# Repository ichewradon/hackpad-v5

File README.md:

# 

My macropad for 3D Modelling with 12 keys in a 4x4 cross, 1 rotary encoder and a LED backlight.

## Features:
- 8 SK6812 MINI-E LEDs for dynamic LED effects
  - Rainbow / Custom Gradient
  - Static Colour
- 1 EC11 Rotary Encoder to control volume with a custom printed dial
- 12 Individually Addressable Keys in a 4x4 cross
- [QMK Firmware](https://github.com/qmk/qmk_firmware) to allow for web-app control and memory after restart

## Overview

This is my hackpad in Fusion360 showing how it's assembled. 

## Case Model

This is my Case Model I made in Fusion360:

## PCB (Printed Circuit Board)

Here's my PCB. It was made in KiCad. The silkscreen was imported from separate vectors.

Schematic:

PCB:

## BoM (Bill of Materials)
- 12x MX-Style Switches
- 12x DSA Keycaps
- 1x EC11 Rotary Encoder
- 13x 1N4148 Diodes
- 8x SK6812 MINI-E LEDs
- 1x Seeed XIAO RP2040

<div align="center">
  
</div>

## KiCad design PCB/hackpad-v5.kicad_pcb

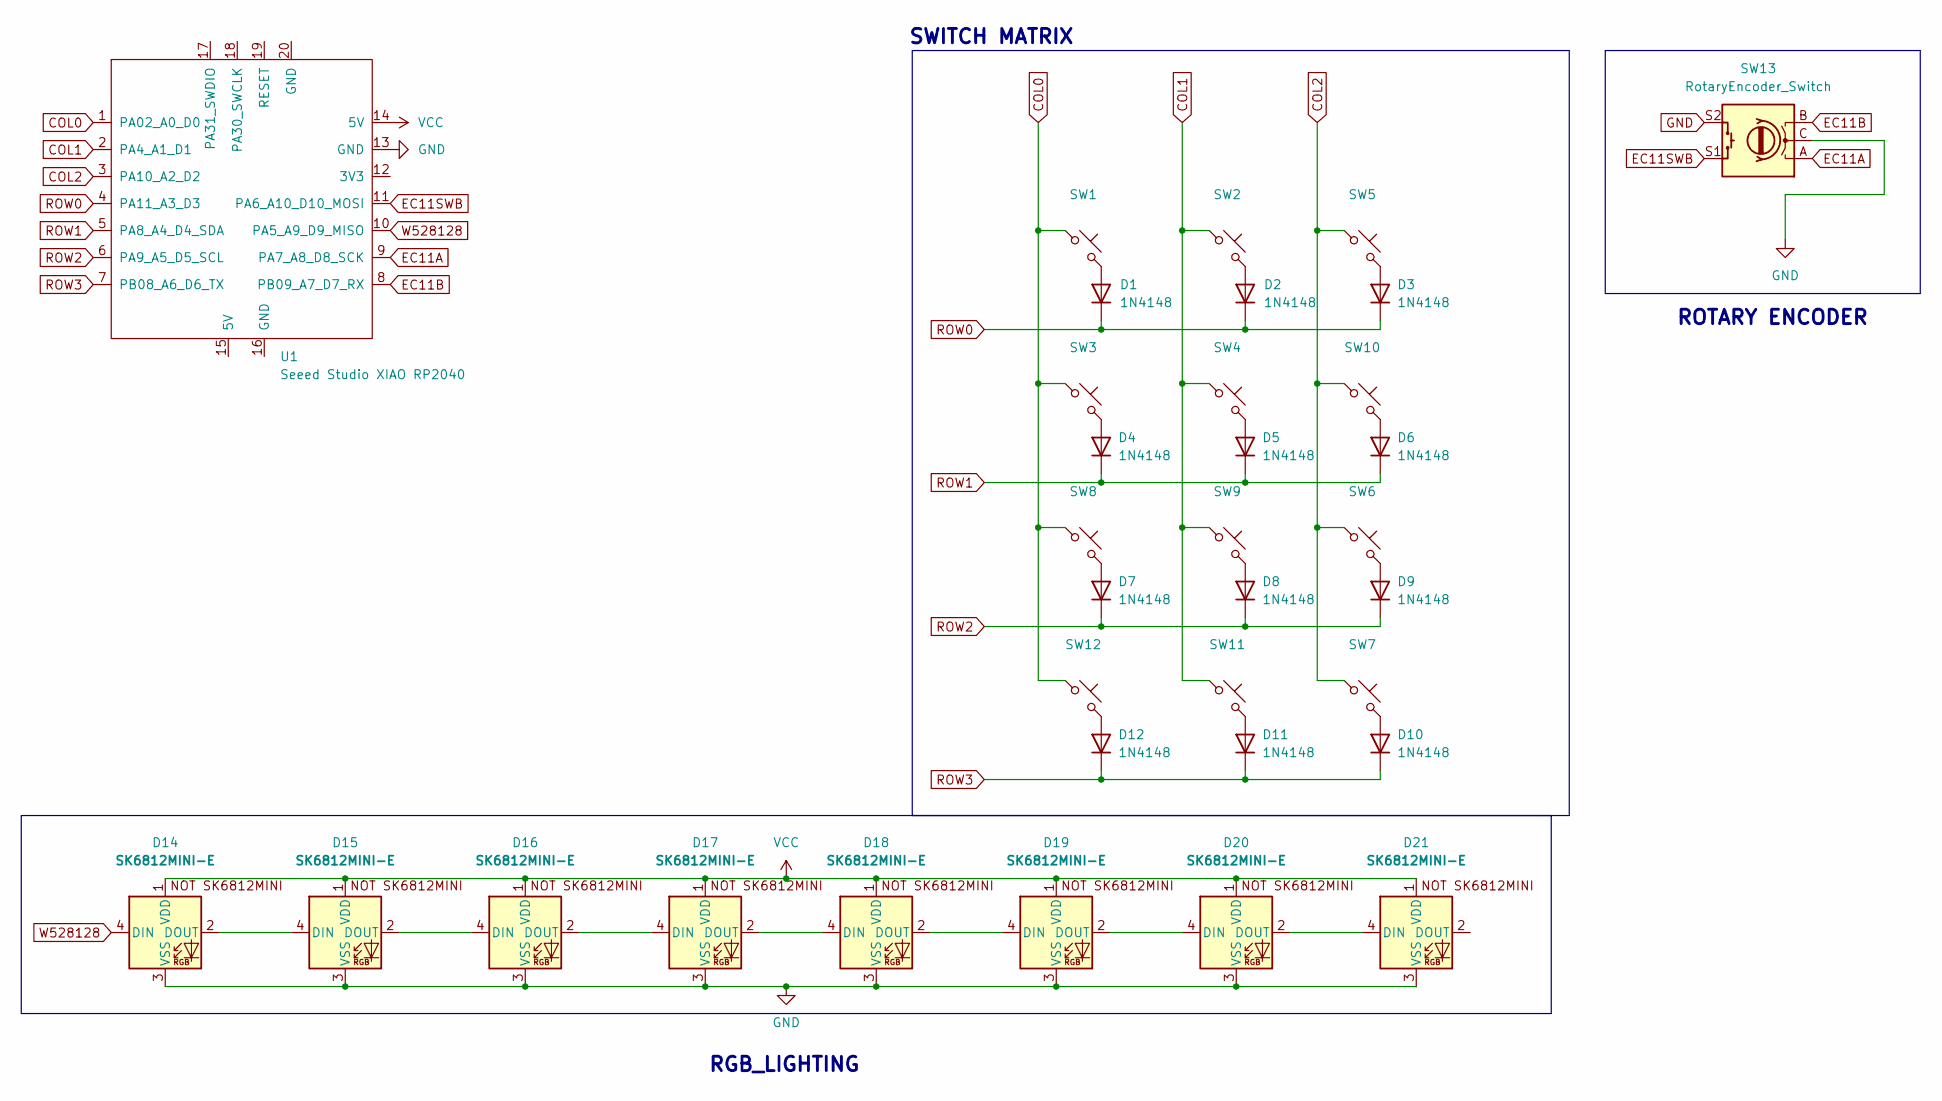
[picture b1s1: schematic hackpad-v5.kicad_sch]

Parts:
D1, D2, D3, D4, D5, D6, D7, D8, D9, D10, D11, D12: 1N4148; D_DO-35_SOD27_P7.62mm_Horizontal
D14, D15, D16, D17, D18, D19, D20, D21: SK6812MINI-E; SK6812MINI-E_fixed
SW1, SW2, SW3, SW4, SW5, SW6, SW7, SW8, SW9, SW10, SW11, SW12: SW_Push_45deg; SW_Cherry_MX_1.00u_PCB
SW13: RotaryEncoder_Switch; RotaryEncoder_Alps_EC11E-Switch_Vertical_H20mm
U1: Seeed Studio XIAO RP2040; XIAO-Generic-Hybrid-14P-2.54-21X17.8MM

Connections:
COL0: SW1.1, SW3.1, SW8.1, SW12.1, U1.1 (PA02_A0_D0)
COL1: SW2.1, SW4.1, SW9.1, SW11.1, U1.2 (PA4_A1_D1)
COL2: SW5.1, SW6.1, SW7.1, SW10.1, U1.3 (PA10_A2_D2)
EC11A: SW13.A, U1.9 (PA7_A8_D8_SCK)
EC11B: SW13.B, U1.8 (PB09_A7_D7_RX)
EC11SWA: U1.12 (3V3)
EC11SWB: SW13.S1, U1.11 (PA6_A10_D10_MOSI)
GND: D14.3 (VSS), D15.3 (VSS), D16.3 (VSS), D17.3 (VSS), D18.3 (VSS), D19.3 (VSS), D20.3 (VSS), D21.3 (VSS), SW13.C, SW13.S2, U1.13 (GND)
unnamed: D1.2 (A), SW1.2
unnamed: D2.2 (A), SW2.2
unnamed: D3.2 (A), SW5.2
unnamed: D4.2 (A), SW3.2
unnamed: D5.2 (A), SW4.2
unnamed: D6.2 (A), SW10.2
unnamed: D7.2 (A), SW8.2
unnamed: D8.2 (A), SW9.2
unnamed: D9.2 (A), SW6.2
unnamed: D10.2 (A), SW7.2
unnamed: D11.2 (A), SW11.2
unnamed: D12.2 (A), SW12.2
unnamed: D14.2 (DOUT), D15.4 (DIN)
unnamed: D15.2 (DOUT), D16.4 (DIN)
unnamed: D16.2 (DOUT), D17.4 (DIN)
unnamed: D17.2 (DOUT), D18.4 (DIN)
unnamed: D18.2 (DOUT), D19.4 (DIN)
unnamed: D19.2 (DOUT), D20.4 (DIN)
unnamed: D20.2 (DOUT), D21.4 (DIN)
ROW0: D1.1 (K), D2.1 (K), D3.1 (K), U1.4 (PA11_A3_D3)
ROW1: D4.1 (K), D5.1 (K), D6.1 (K), U1.5 (PA8_A4_D4_SDA)
ROW2: D7.1 (K), D8.1 (K), D9.1 (K), U1.6 (PA9_A5_D5_SCL)
ROW3: D10.1 (K), D11.1 (K), D12.1 (K), U1.7 (PB08_A6_D6_TX)
VCC: D14.1 (VDD), D15.1 (VDD), D16.1 (VDD), D17.1 (VDD), D18.1 (VDD), D19.1 (VDD), D20.1 (VDD), D21.1 (VDD), U1.14 (5V)
W528128: D14.4 (DIN), U1.10 (PA5_A9_D9_MISO)

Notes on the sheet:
ROTARY ENCODER
SWITCH MATRIX
RGB_LIGHTING

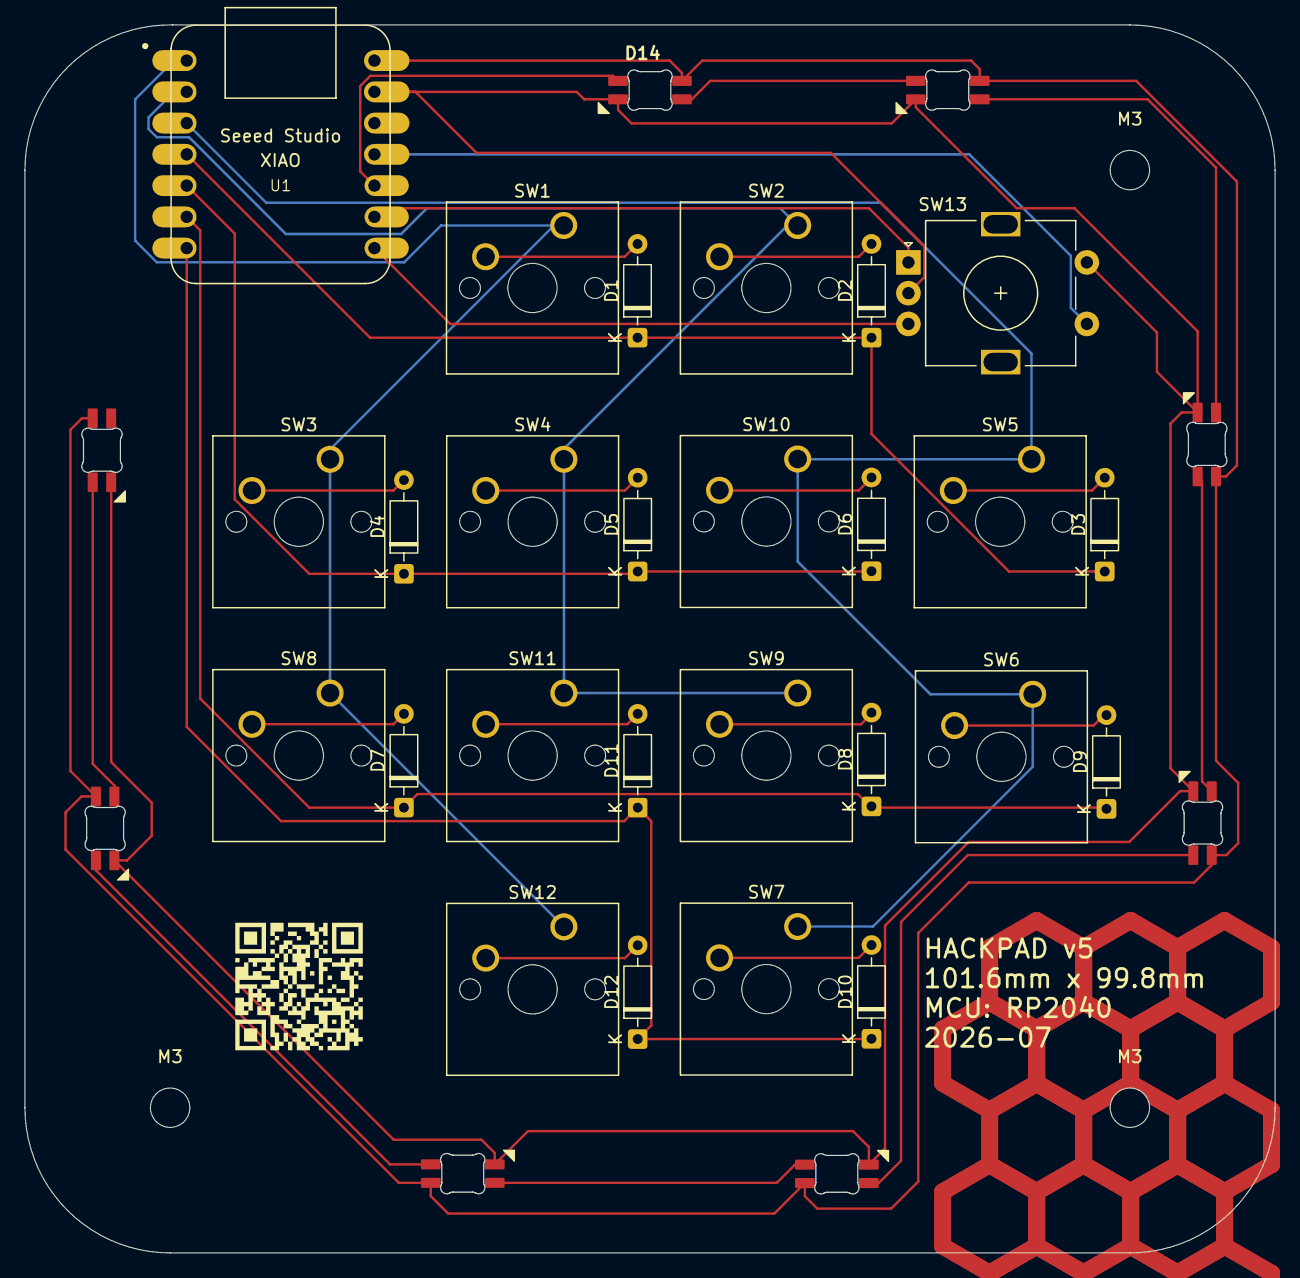
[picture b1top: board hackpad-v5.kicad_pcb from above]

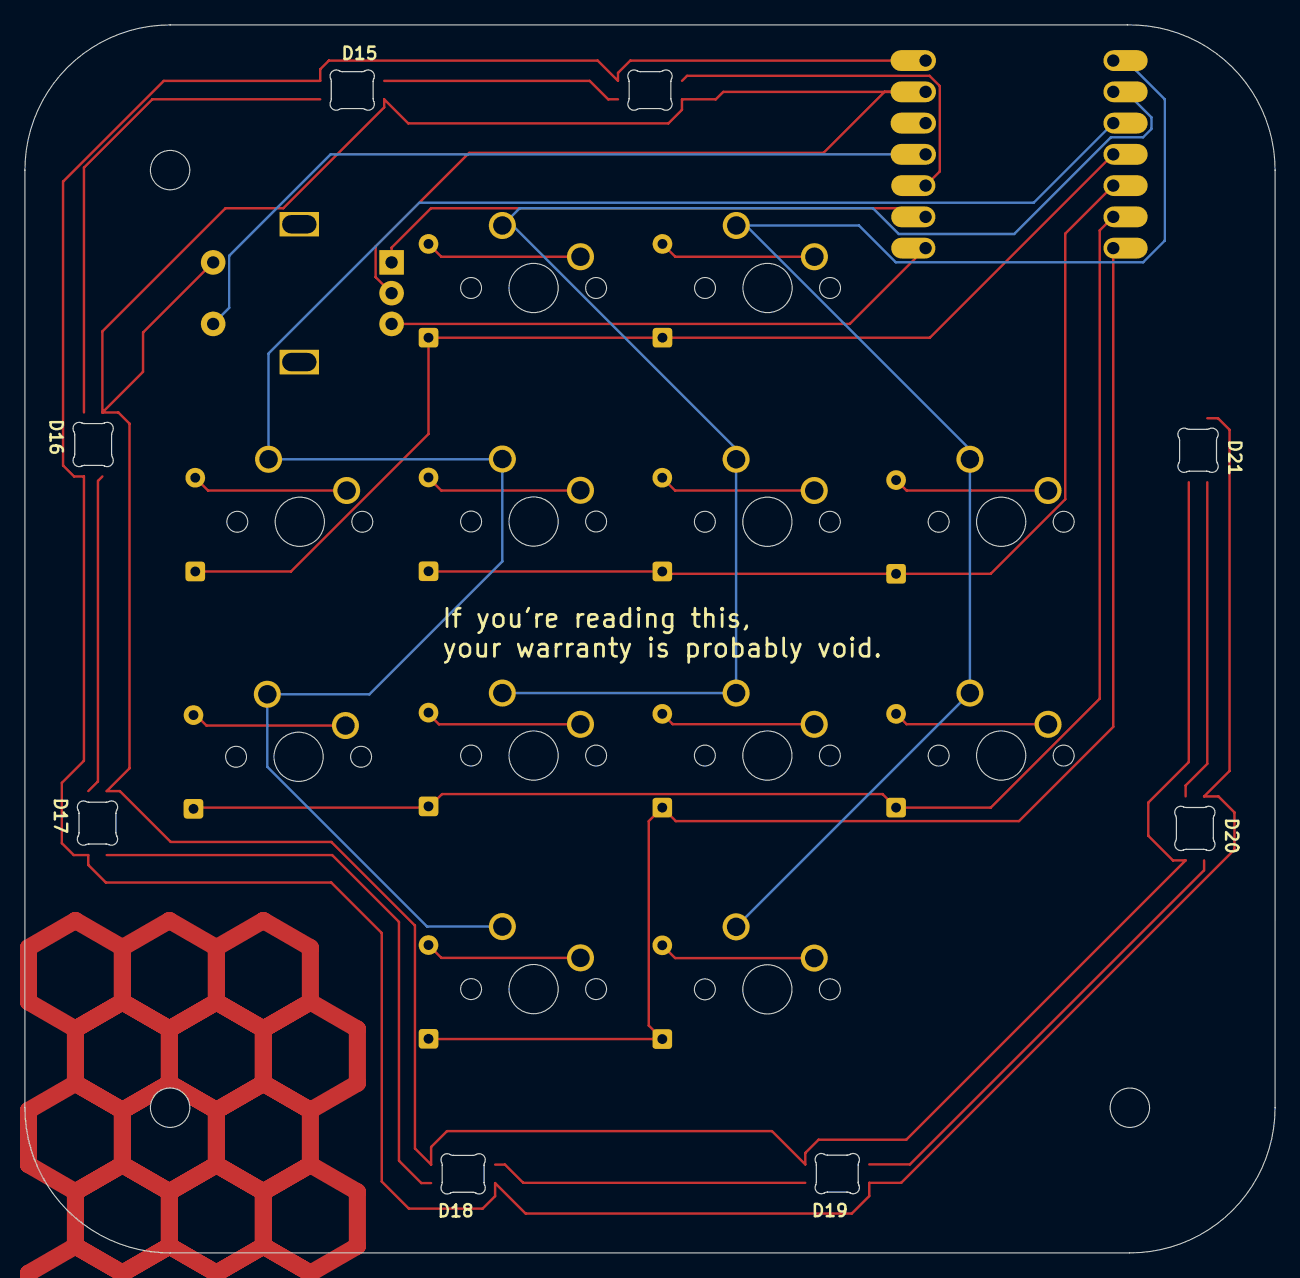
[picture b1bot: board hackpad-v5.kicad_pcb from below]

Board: 2 copper layers, 101.6 x 99.8 mm, 37 parts (8 on the bottom side), 32 nets.

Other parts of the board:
M3, M3#2, M3#3: MountingHole_3.2mm_M3
